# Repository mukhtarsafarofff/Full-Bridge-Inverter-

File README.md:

(ENG) The following design shows the standard module  I have identified the four mosfets rigged as an H-bridge or a full bridge network. I know that in any H-bridge the mosfets are configured to conduct diagonally for implementing the intended push pull conduction across the transformeror the connected load. This implies that pin#11 of the IC is high during this instance, which keeps the left side BC547 switch ON. In this situation the following things happen withing the left side BC547 stage:  
1) The 100uF capacitor charges up via the 1N4007 diode and the low side mosfet connected with its negative terminal.
2) This charge is temporarily stored inside the capacitor and may be assumed to be equal to the supply voltage.
3) Now as soon as the logic across the SG3525 reverts with the subsequent oscillating cycle, the pin#11 goes low, which instantly switches OFF the associated BC547.
4) With BC547 switched OFF, the supply voltage at the cathode of the 1N007 now reaches the gate of the connected mosfet, however this voltage is now reinforced with the stored voltage inside capacitor which is also almost equal to the supply level.
5) This results in a doubling effect and enables a raised 2X voltage at the gate of the relevant mosfet.
6) This condition instantly hard triggers the mosfet into conduction, which pushes the voltage across the corresponding opposite low side mosfet.
7) During this situation the capacitor is forced to discharge quickly and the mosfet is able to conduct only for so long the stored charge of this capacitor is able to sustain.
8) The value of the capacitor is selected such that the capacitor is able to adequately hold the charge for each ON/OFF period of the push pull oscillations.

(DEU) Das folgende Design zeigt das Standardmodul, das in jeden gewöhnlichen SG3525-Wechselrichter über die Ausgangspins des ICs integriert werden kann, um einen hocheffizienten SG3525-Vollbrücken- oder H-Brücken-Wechselrichter zu realisieren. Mit Bezug auf das obige Diagramm habe ich die vier MOSFETs identifiziert, die als H-Brücke oder Vollbrücken-Netzwerk verschaltet sind. Ich weiß, dass in jeder H-Brücke die MOSFETs diagonal geschaltet sind, um die beabsichtigte Gegentaktleitung über den Transformator oder die angeschlossene Last zu implementieren. Dies impliziert, dass Pin#11 des ICs in diesem Moment auf High ist, was den linken BC547-Schalter eingeschaltet hält.  In dieser Situation geschehen die folgenden Dinge innerhalb der linken BC547-Stufe:
1) Der 100uF-Kondensator lädt sich über die 1N4007-Diode und den mit seinem negativen Anschluss verbundenen Low-Side-MOSFET auf.
2) Diese Ladung wird vorübergehend im Kondensator gespeichert und kann als gleich der Versorgungsspannung angenommen werden.
3) Sobald die Logik des SG3525 im nächsten Oszillationszyklus umschaltet, geht Pin#11 auf Low, was den zugehörigen BC547 sofort ausschaltet.
4) Mit ausgeschaltetem BC547 erreicht die Versorgungsspannung an der Kathode der 1N4007 nun das Gate des angeschlossenen MOSFETs, jedoch wird diese Spannung jetzt durch die im Kondensator gespeicherte Spannung verstärkt, die ebenfalls nahezu der Versorgungsspannung entspricht.
5) Dies führt zu einem Dopplungseffekt und ermöglicht eine erhöhte 2X-Spannung am Gate des entsprechenden MOSFETs.
6) Diese Bedingung schaltet den MOSFET sofort hart ein, was die Spannung über den entsprechenden gegenüberliegenden Low-Side-MOSFET drückt.
7) In dieser Situation wird der Kondensator gezwungen, sich schnell zu entladen, und der MOSFET kann nur so lange leiten, wie die gespeicherte Ladung dieses Kondensators ausreicht.
8) Der Wert des Kondensators wird so gewählt, dass der Kondensator die Ladung für jede Ein/Aus-Periode der Gegentakt-Oszillationen ausreichend halten kann.

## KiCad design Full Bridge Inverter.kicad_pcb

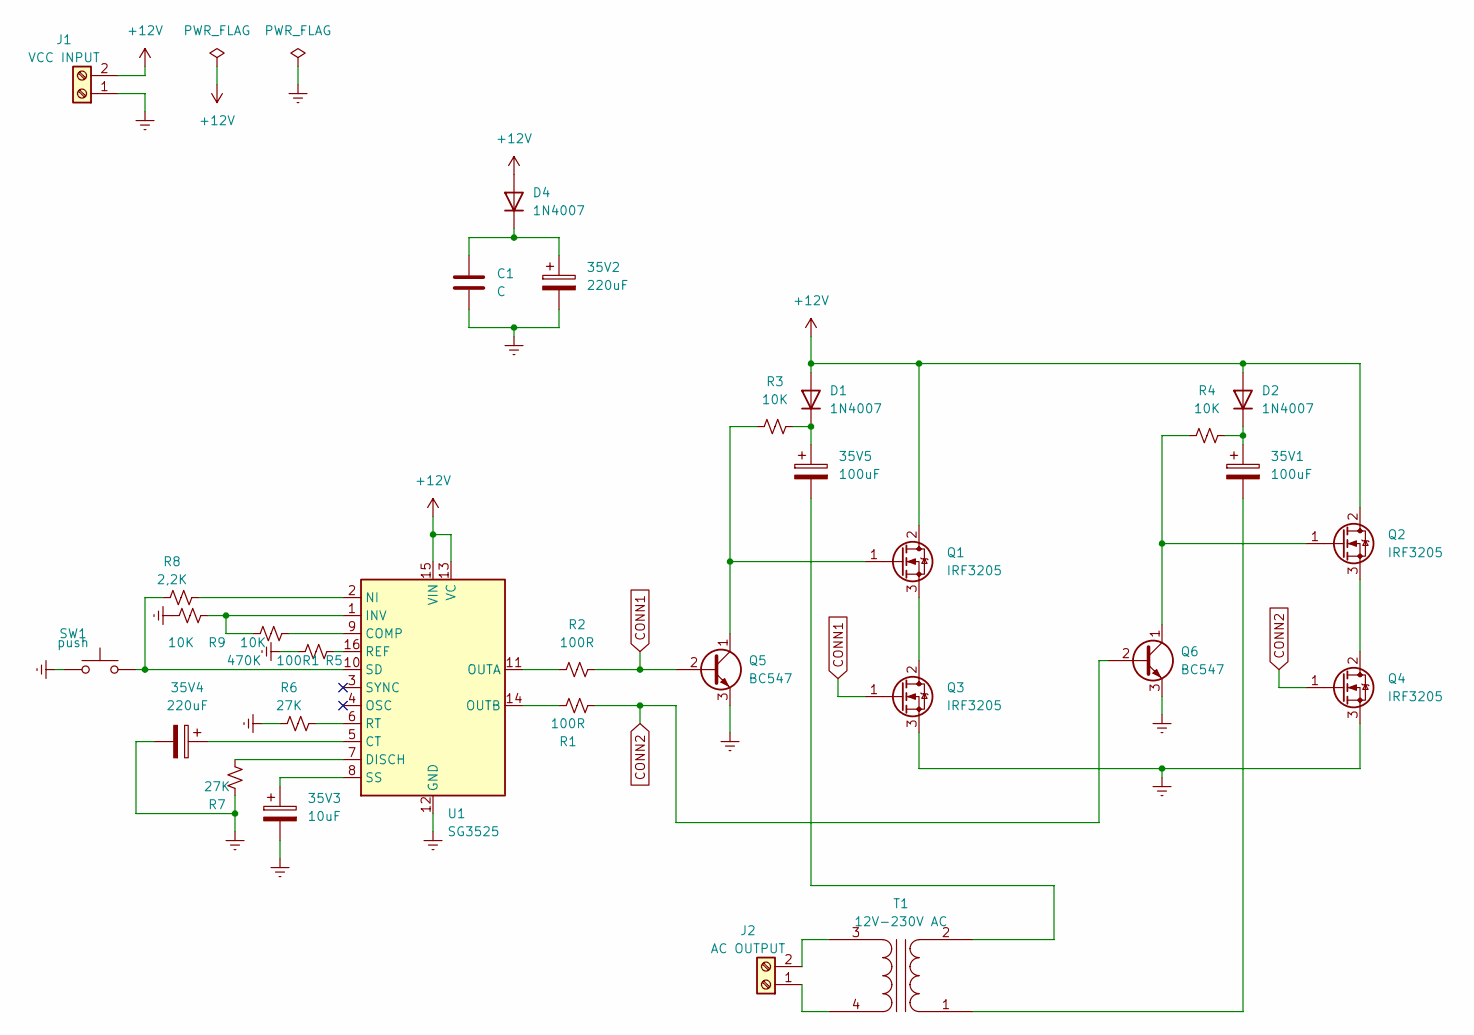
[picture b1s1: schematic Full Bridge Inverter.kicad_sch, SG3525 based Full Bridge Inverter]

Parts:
35V1, 35V5: 100uF; CP_Radial_D10.0mm_P5.00mm
35V2, 35V4: 220uF; CP_Radial_D12.5mm_P5.00mm
35V3: 10uF; CP_Radial_D8.0mm_P5.00mm
100R1: 10K; R_Axial_DIN0309_L9.0mm_D3.2mm_P15.24mm_Horizontal
C1: C; C_Disc_D7.5mm_W5.0mm_P7.50mm
D1, D2, D4: 1N4007; D_DO-41_SOD81_P10.16mm_Horizontal
J1: VCC INPUT; Altech_AK300_1x02_P5.00mm_45-Degree
J2: AC OUTPUT; Altech_AK300_1x02_P5.00mm_45-Degree
Q1, Q2, Q3, Q4: IRF3205; TO-220-3_Vertical
Q5, Q6: BC547; TO-92_Inline
R1, R2: 100R; R_Axial_DIN0309_L9.0mm_D3.2mm_P15.24mm_Horizontal
R3, R4, R9: 10K; R_Axial_DIN0309_L9.0mm_D3.2mm_P15.24mm_Horizontal
R5: 470K; R_Axial_DIN0309_L9.0mm_D3.2mm_P15.24mm_Horizontal
R6, R7: 27K; R_Axial_DIN0309_L9.0mm_D3.2mm_P15.24mm_Horizontal
R8: 2,2K; R_Axial_DIN0309_L9.0mm_D3.2mm_P15.24mm_Horizontal
SW1: push; SW_PUSH_6mm_H9.5mm
T1: 12V-230V AC; Transformer_Toroid_Horizontal_D9.0mm_Amidon-T30
U1: SG3525; DIP-16_W7.62mm

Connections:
+12V: D1.2 (A), D2.2 (A), D4.2 (A), J1.2, Q1.2 (D), Q2.2 (D), U1.13 (VC), U1.15 (VIN)
CONN1: Q3.1 (G), Q5.2 (B), R2.2
CONN2: Q4.1 (G), Q6.2 (B), R1.2
Earth: 35V2.2, 35V3.2, 35V4.2, C1.2, J1.1, Q3.3 (S), Q4.3 (S), Q5.3 (E), Q6.3 (E), R5.1, R6.1, R7.1, R9.2, SW1.1, U1.12 (GND)
unnamed: 35V5.1, D1.1 (K), R3.2
unnamed: 35V1.1, D2.1 (K), R4.1
unnamed: 35V2.1, C1.1, D4.1 (K)
unnamed: J2.1, T1.4 (SB)
unnamed: J2.2, T1.3 (SA)
unnamed: Q1.1 (G), Q5.1 (C), R3.1
unnamed: Q1.3 (S), Q3.2 (D)
unnamed: Q2.1 (G), Q6.1 (C), R4.2
unnamed: Q2.3 (S), Q4.2 (D)
unnamed: 35V1.2, T1.1 (AA)
unnamed: 35V5.2, T1.2 (AB)
unnamed: 100R1.1, U1.9 (COMP)
unnamed: 35V4.1, U1.5 (CT)
unnamed: R7.2, U1.7 (DISCH)
unnamed: 100R1.2, R9.1, U1.1 (INV)
unnamed: R8.1, U1.2 (NI)
unnamed: R2.1, U1.11 (OUTA)
unnamed: R1.1, U1.14 (OUTB)
unnamed: R5.2, U1.16 (REF)
unnamed: R6.2, U1.6 (RT)
unnamed: R8.2, SW1.2, U1.10 (SD)
unnamed: 35V3.1, U1.8 (SS)

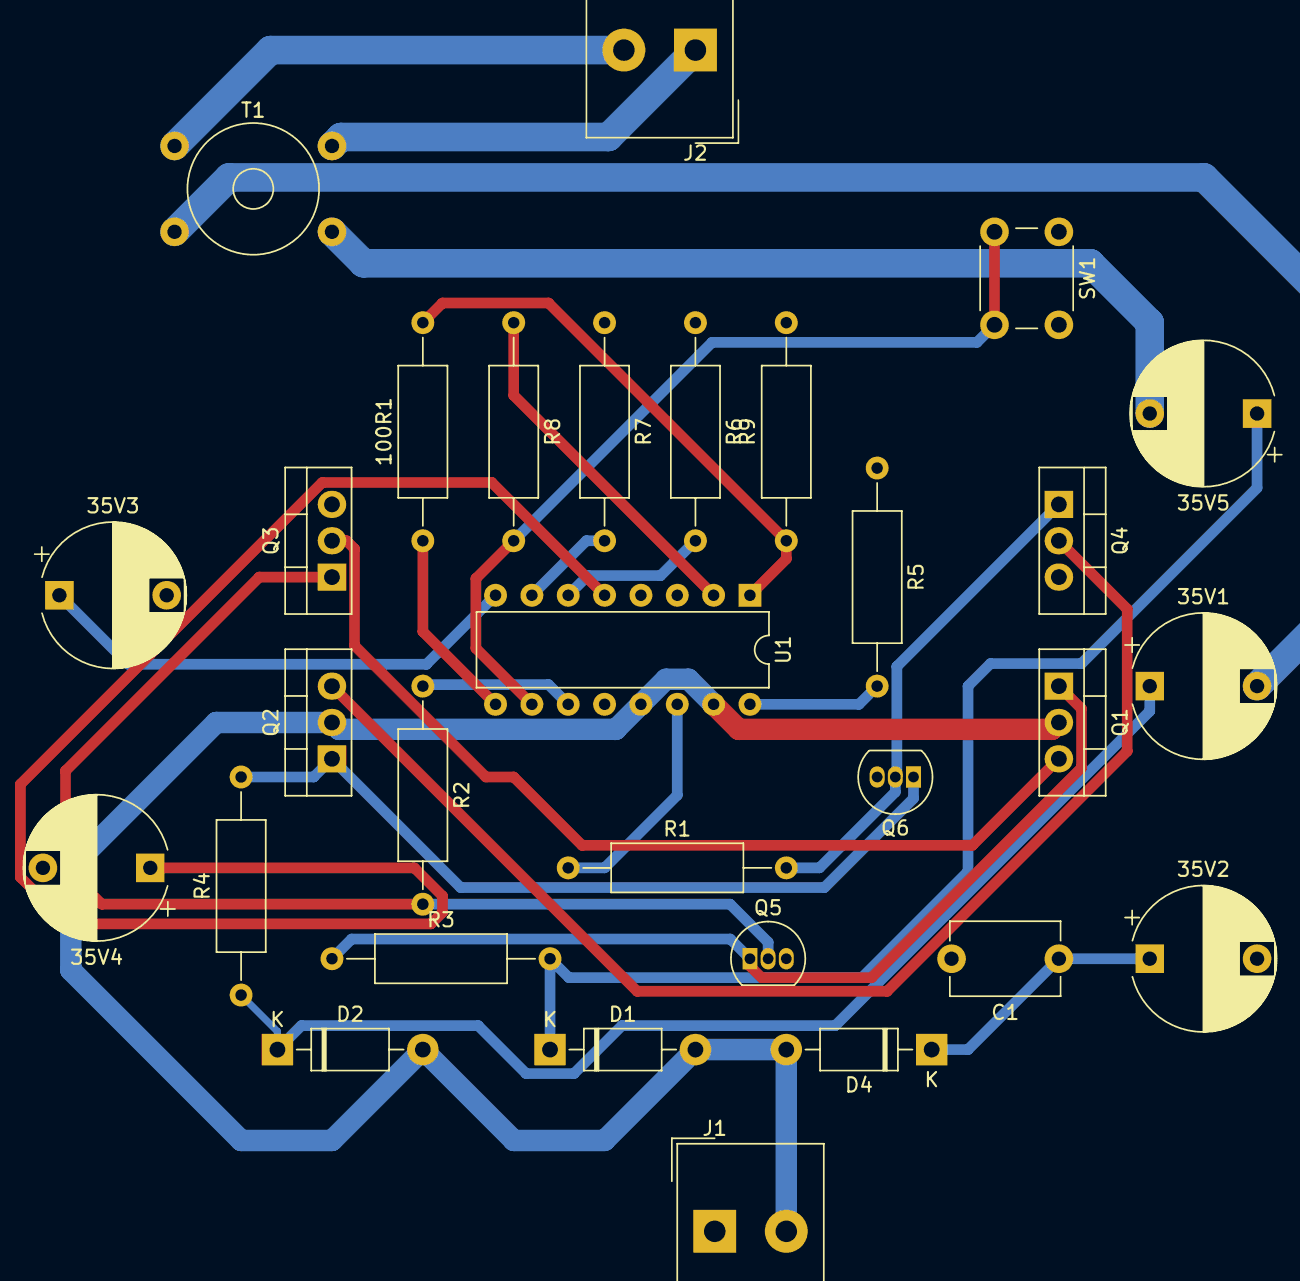
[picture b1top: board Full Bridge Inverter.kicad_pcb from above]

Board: 2 copper layers, 30 parts (0 on the bottom side), 26 nets.

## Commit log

2024-05-07 Full Bridge Inverter is accomplished
